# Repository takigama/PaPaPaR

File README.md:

# PaPaPaR

Short for Paste and Pick and Place and Reflow.

This project is an attempt to create a board that will do solder paste,
pick and place and lastly reflow. Initially I'll be aiming souly at the
pick and place stuff but theres enough componentry on the board to
control the paste and reflow components as well.

It does have enough componentry to also do a single extruder 3d printer
which wasnt exactly a goal, but was a handy alternative function for
the board. 

The board itself is reasonably compact but not a huge amount of work
has gone into it yet.

## Usage

Well, none yet. Haven't even printed the board yet. Currently using
RAMPS as a test bed.

This project is based on the STM32F103 chip and will (at least
initially) use the STM32duino code base with the arduino software
stack for making the thing "go"

You'll need kicad if you want to see the board and once i have a
working model, i'll share it as a project on oshpark!

## Thanks

Thanks go to the folk who do arduino, the folk who do stm32duino, to
the folk who do KiCad and many others probably. As of the current version
the only hardware designer is me... Im also the only coder... and the only
everything else but would welcome others

## Where it starts

The first version will be quite simple. Designed to be controlled with
2 "wiichucks", there is an expectation of having a camera and the pick
and place will be done "manually" but all electrically - i.e. you'll
place componets using joystick with some interesting hot keys and a bit
of camera work.

## It Looks Like This:

## What you need

- 3 Steppers (one for the pump)
- Perastaltic pump that can be driving by stepper (or 5-6v DC)
- a pick-up sucktion cup (i have a design for this thats really simple)
- a usb microscope.
- a design for it all to sit on
- a fair amount of imagination and pixie dust!
- a 12v power source

The pump (which is used to hold components) can either be stepper driven
or you can find plenty of 5-6v aquarium pumps on ebay that should surfice
but they want to be less than 1A.

Currently im working on the design of the actual platform for the whole
unit and it will look like a distant cousin of something like the mendel
90 (my fave 3d print) but with a stationary platform and a cartesian type
head. I was VERY tempted to do a delta but am shelving that idea for now

Currently there also exists no code but watch this space - some will
definitely be borrowed from the sprinter/marlin code bases but no code
yet exists.

## Things To Note

1. Its designed to be possible to hand solder (which is how I will build
it)

2. I take no responsibility if it does anything negative!

3. Its alpha

4. Im not the worlds greatest hardware designer (or even a good one)!

5. Currently doesnt have a license - feel free to do as you will, but will
ultimately be licensed under a compatible open source license (GPL for code
as an example)

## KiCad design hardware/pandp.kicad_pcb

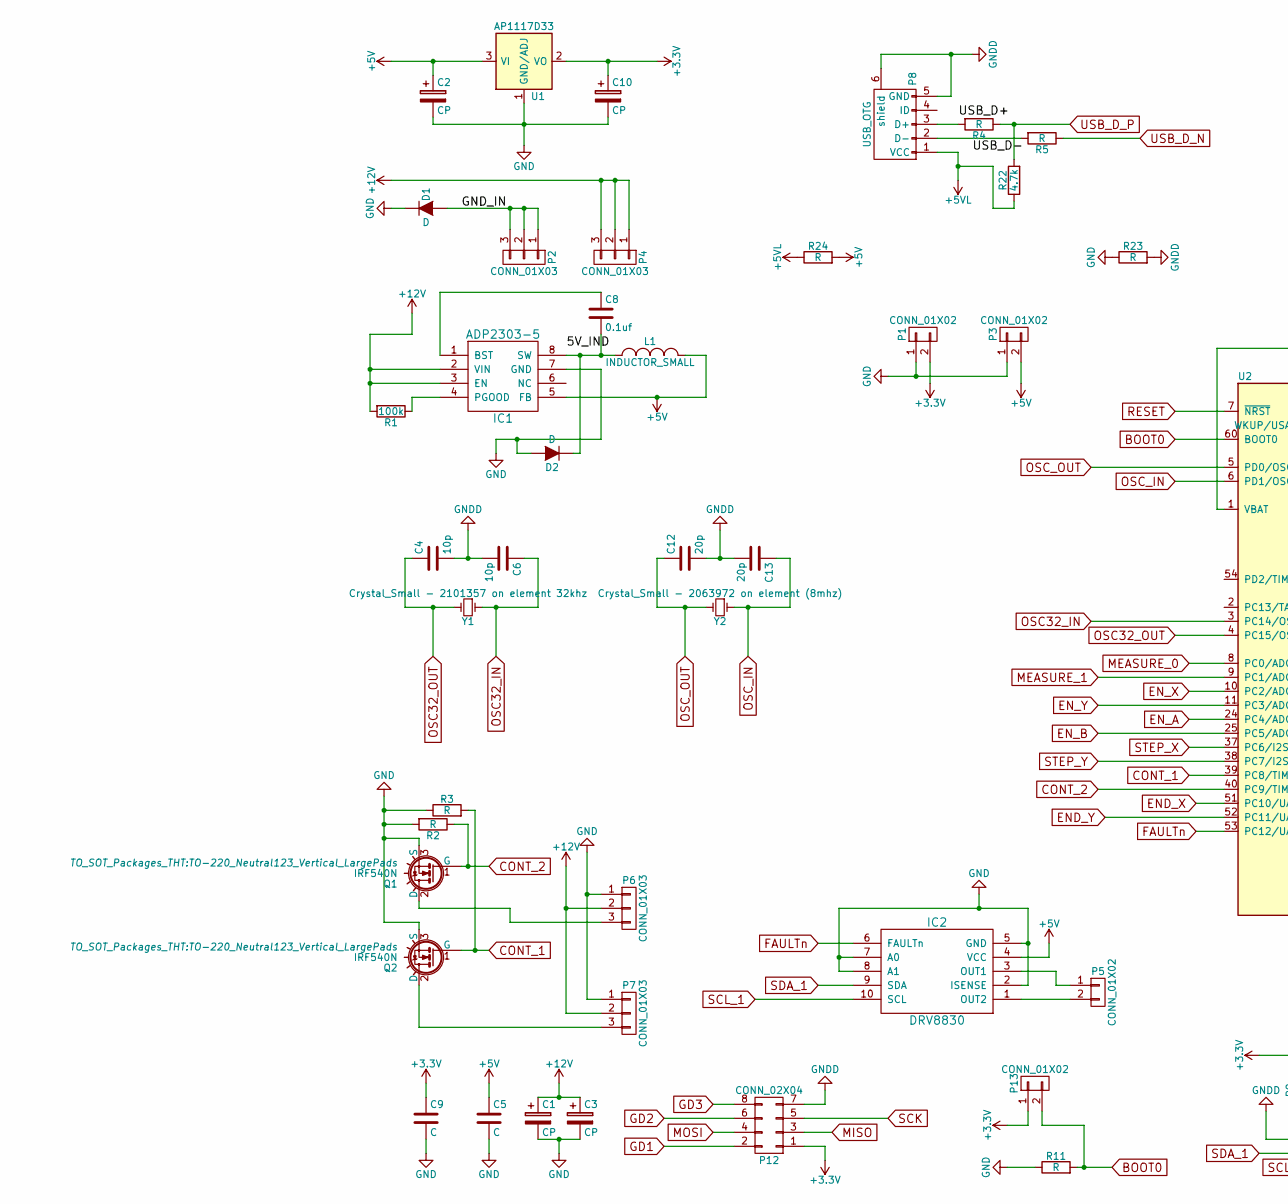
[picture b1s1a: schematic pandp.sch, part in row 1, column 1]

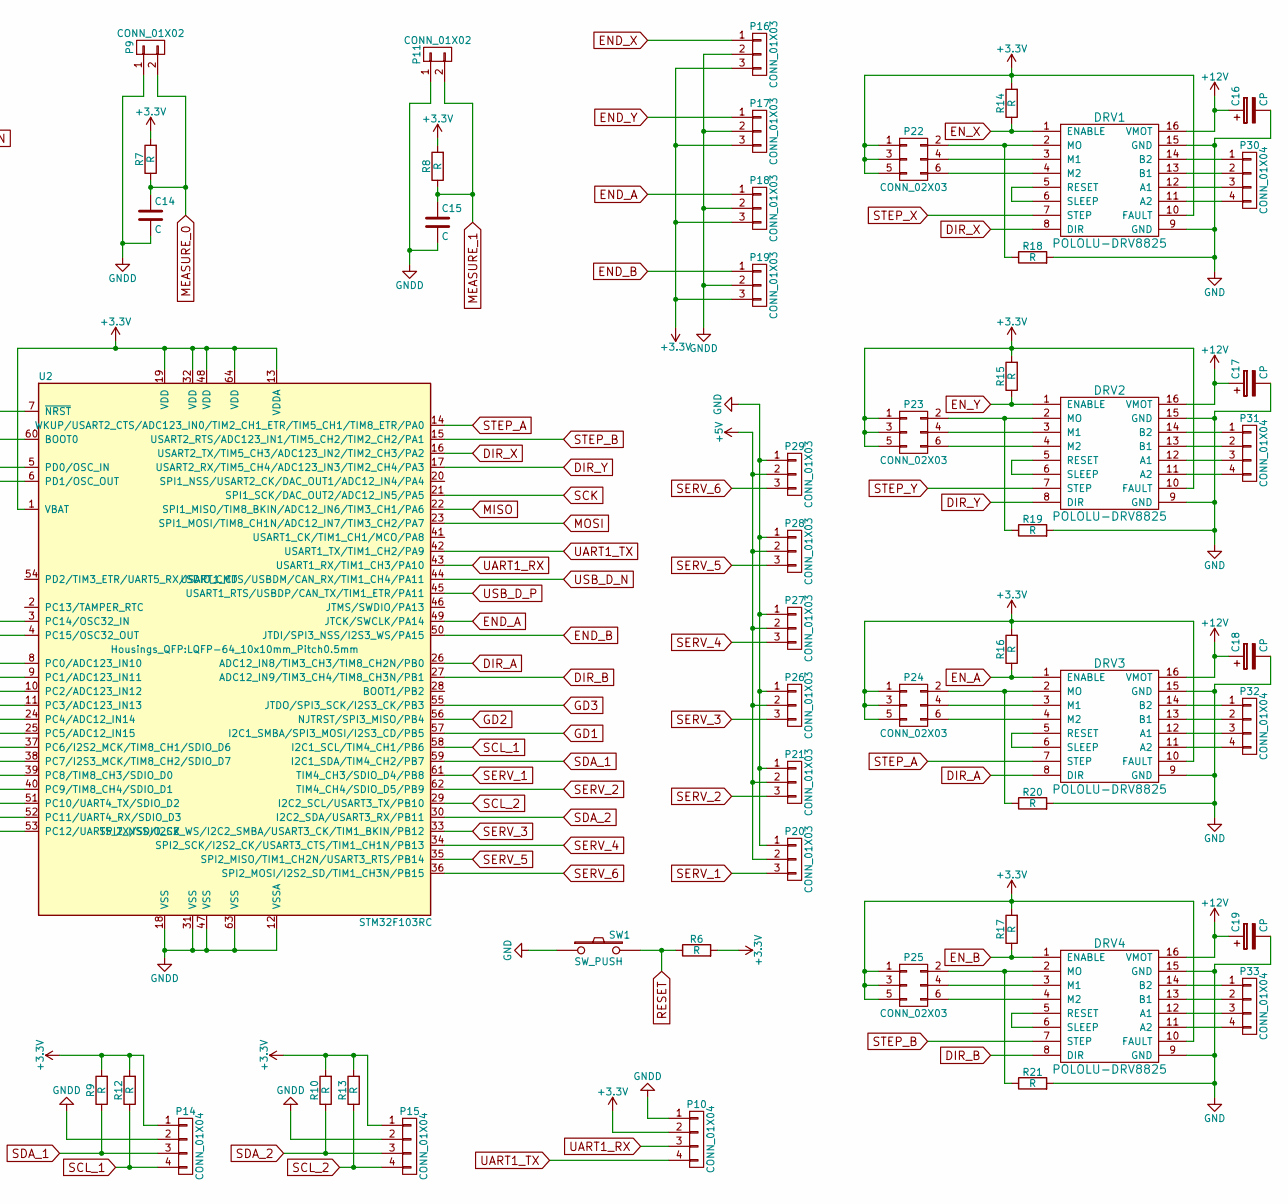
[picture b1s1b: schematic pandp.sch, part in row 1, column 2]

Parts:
C1, C2, C3, C10, C16, C17, C18, C19: CP; SMD-1210_Pol
C4, C6: 10p; C_0805_HandSoldering
C5, C9, C14, C15: C; C_0805_HandSoldering
C8: 0.1uf; C_0805_HandSoldering
C12, C13: 20p; C_0805_HandSoldering
D1, D2: D; SMB_Handsoldering
DRV1, DRV2, DRV3, DRV4: POLOLU-DRV8825
IC1: ADP2303-5; SOIC-8_3.9x4.9mm_Pitch1.27mm
IC2: DRV8830; TSSOP-10_3x3mm_Pitch0.5mm
L1: INDUCTOR_SMALL; Choke_SMD_7.3x7.3_H3.5
P1, P3, P5, P9, P11, P13: CONN_01X02; Pin_Header_Straight_1x02
P2, P4, P6, P7, P16, P17, P18, P19, P20, P21, P26, P27, P28, P29: CONN_01X03; Pin_Header_Straight_1x03
P8: USB_OTG; USB_Micro-B-OshPark
P10, P14, P15, P30, P31, P32, P33: CONN_01X04; Pin_Header_Straight_1x04
P12: CONN_02X04; Pin_Header_Straight_2x04
P22, P23, P24, P25: CONN_02X03; Pin_Header_Straight_2x03
Q1, Q2: IRF540N; TO-220_Neutral123_Vertical_LargePads
R1: 100k; R_0805_HandSoldering
R2, R3, R4, R5, R6, R7, R8, R9, R10, R11, R12, R13, R14, R15, R16, R17, R18, R19, R20, R21: R; R_0805_HandSoldering
R22: 4.7k; R_0805_HandSoldering
R23, R24: R; R_0402
SW1: SW_PUSH; SW_SPST_FSMSM
U1: AP1117D33; SOT-223
U2: STM32F103RC; LQFP-64_10x10mm_Pitch0.5mm
Y1: Crystal_Small - 2101357 on element 32khz; ABM3
Y2: Crystal_Small - 2063972 on element (8mhz); Crystal_HC49-SD_SMD

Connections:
+3V3: C9.1, C10.1, DRV1.10 (FAULT), DRV2.10 (FAULT), DRV3.10 (FAULT), DRV4.10 (FAULT), P1.2, P10.2, P12.1, P13.1, P14.1, P15.1, P16.3, P17.3, P18.3, P19.3, P22.1, P22.3, P22.5, P23.1, P23.3, P23.5, P24.1, P24.3, P24.5, P25.1, P25.3, P25.5, R6.2, R7.2, R8.2, R9.2, R10.2, R12.2, R13.2, R14.2, R15.2, R16.2, R17.2, U1.2 (VO), U2.1 (VBAT), U2.13 (VDDA), U2.19 (VDD), U2.32 (VDD), U2.48 (VDD), U2.64 (VDD)
+5V: C2.1, C5.1, IC1.5 (FB), IC2.4 (VCC), L1.2, P3.2, P20.2, P21.2, P26.2, P27.2, P28.2, P29.2, R24.2, U1.3 (VI)
+5VL: P8.1 (VCC), R22.1, R24.1
+12V: C1.1, C3.1, C16.1, C17.1, C18.1, C19.1, DRV1.16 (VMOT), DRV2.16 (VMOT), DRV3.16 (VMOT), DRV4.16 (VMOT), IC1.2 (VIN), IC1.3 (EN), P4.1, P4.2, P4.3, P6.2, P7.2, R1.2
/GND_IN: D1.2 (A), P2.1, P2.2, P2.3
BOOT0: P13.2, R11.2, U2.60 (BOOT0)
CONT_1: Q2.1 (G), R3.2, U2.39 (PC8/TIM8_CH3/SDIO_D0)
CONT_2: Q1.1 (G), R2.1, U2.40 (PC9/TIM8_CH4/SDIO_D1)
DIR_A: DRV3.8 (DIR), U2.26 (ADC12_IN8/TIM3_CH3/TIM8_CH2N/PB0)
DIR_B: DRV4.8 (DIR), U2.27 (ADC12_IN9/TIM3_CH4/TIM8_CH3N/PB1)
DIR_X: DRV1.8 (DIR), U2.16 (USART2_TX/TIM5_CH3/ADC123_IN2/TIM2_CH3/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)
DIR_Y: DRV2.8 (DIR), U2.17 (USART2_RX/TIM5_CH4/ADC123_IN3/TIM2_CH4/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)
END_A: P18.1, U2.49 (JTCK/SWCLK/PA14)
END_B: P19.1, U2.50 (JTDI/SPI3_NSS/I2S3_WS/PA15)
END_X: P16.1, U2.51 (PC10/UART4_TX/SDIO_D2)
END_Y: P17.1, U2.52 (PC11/UART4_RX/SDIO_D3)
EN_A: DRV3.1 (ENABLE), R16.1, U2.24 (PC4/ADC12_IN14)
EN_B: DRV4.1 (ENABLE), R17.1, U2.25 (PC5/ADC12_IN15)
EN_X: DRV1.1 (ENABLE), R14.1, U2.10 (PC2/ADC123_IN12)
EN_Y: DRV2.1 (ENABLE), R15.1, U2.11 (PC3/ADC123_IN13)
FAULTn: IC2.6 (FAULTn), U2.53 (PC12/UART5_TX/SDIO_CK)
GD1: P12.2, U2.57 (I2C1_SMBA/SPI3_MOSI/I2S3_CD/PB5)
GD2: P12.6, U2.56 (NJTRST/SPI3_MISO/PB4)
GD3: P12.8, U2.55 (JTDO/SPI3_SCK/I2S3_CK/PB3)
GND: C1.2, C2.2, C3.2, C5.2, C9.2, C10.2, C16.2, C17.2, C18.2, C19.2, D1.1 (K), D2.2 (A), DRV1.9 (GND), DRV1.15 (GND), DRV2.9 (GND), DRV2.15 (GND), DRV3.9 (GND), DRV3.15 (GND), DRV4.9 (GND), DRV4.15 (GND), IC1.7 (GND), IC2.2 (ISENSE), IC2.5 (GND), IC2.7 (A0), IC2.8 (A1), P1.1, P3.1, P6.1, P7.1, P20.1, P21.1, P26.1, P27.1, P28.1, P29.1, Q1.3 (S), Q2.3 (S), R2.2, R3.1, R11.1, R18.2, R19.2, R20.2, R21.2, R23.1, SW1.1, U1.1 (GND/ADJ)
GNDD: C4.2, C6.2, C12.2, C13.2, C14.2, C15.2, P8.5 (GND), P8.6 (shield), P9.1, P10.1, P11.1, P12.7, P14.2, P15.2, P16.2, P17.2, P18.2, P19.2, R23.2, U2.12 (VSSA), U2.18 (VSS), U2.31 (VSS), U2.47 (VSS), U2.63 (VSS)
MEASURE_0: C14.1, P9.2, R7.1, U2.8 (PC0/ADC123_IN10)
MEASURE_1: C15.1, P11.2, R8.1, U2.9 (PC1/ADC123_IN11)
MISO: P12.3, U2.22 (SPI1_MISO/TIM8_BKIN/ADC12_IN6/TIM3_CH1/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)
MOSI: P12.4, U2.23 (SPI1_MOSI/TIM8_CH1N/ADC12_IN7/TIM3_CH2/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)
unnamed: C8.1, IC1.1 (BST)
unnamed: C8.2, D2.1 (K), IC1.8 (SW), L1.1
unnamed: DRV1.2 (MO), P22.2, R18.1
unnamed: DRV1.3 (M1), P22.4
unnamed: DRV1.4 (M2), P22.6
unnamed: DRV1.5 (RESET), DRV1.6 (SLEEP)
unnamed: DRV1.11 (A2), P30.4
unnamed: DRV1.12 (A1), P30.3
unnamed: DRV1.13 (B1), P30.2
unnamed: DRV1.14 (B2), P30.1
unnamed: DRV2.2 (MO), P23.2, R19.1
unnamed: DRV2.3 (M1), P23.4
unnamed: DRV2.4 (M2), P23.6
unnamed: DRV2.5 (RESET), DRV2.6 (SLEEP)
unnamed: DRV2.11 (A2), P31.4
unnamed: DRV2.12 (A1), P31.3
unnamed: DRV2.13 (B1), P31.2
unnamed: DRV2.14 (B2), P31.1
unnamed: DRV3.2 (MO), P24.2, R20.1
unnamed: DRV3.3 (M1), P24.4
unnamed: DRV3.4 (M2), P24.6
unnamed: DRV3.5 (RESET), DRV3.6 (SLEEP)
unnamed: DRV3.11 (A2), P32.4
unnamed: DRV3.12 (A1), P32.3
unnamed: DRV3.13 (B1), P32.2
unnamed: DRV3.14 (B2), P32.1
unnamed: DRV4.2 (MO), P25.2, R21.1
unnamed: DRV4.3 (M1), P25.4
unnamed: DRV4.4 (M2), P25.6
unnamed: DRV4.5 (RESET), DRV4.6 (SLEEP)
unnamed: DRV4.11 (A2), P33.4
unnamed: DRV4.12 (A1), P33.3
unnamed: DRV4.13 (B1), P33.2
unnamed: DRV4.14 (B2), P33.1
unnamed: IC1.4 (PGOOD), R1.1
unnamed: IC2.1 (OUT2), P5.2
unnamed: IC2.3 (OUT1), P5.1
unnamed: P6.3, Q1.2 (D)
unnamed: P7.3, Q2.2 (D)
unnamed: P8.2 (D-), R5.2
unnamed: P8.3 (D+), R4.2
OSC32_IN: C6.1, U2.3 (PC14/OSC32_IN), Y1.1
OSC32_OUT: C4.1, U2.4 (PC15/OSC32_OUT), Y1.2
OSC_IN: C13.1, U2.6 (PD1/OSC_OUT), Y2.1
OSC_OUT: C12.1, U2.5 (PD0/OSC_IN), Y2.2
RESET: R6.1, SW1.2, U2.7 (~NRST)
SCK: P12.5, U2.21 (SPI1_SCK/DAC_OUT2/ADC12_IN5/PA5)
SCL_1: IC2.10 (SCL), P14.4, R12.1, U2.58 (I2C1_SCL/TIM4_CH1/PB6)
SCL_2: P15.4, R13.1, U2.29 (I2C2_SCL/USART3_TX/PB10)
SDA_1: IC2.9 (SDA), P14.3, R9.1, U2.59 (I2C1_SDA/TIM4_CH2/PB7)
SDA_2: P15.3, R10.1, U2.30 (I2C2_SDA/USART3_RX/PB11)
SERV_1: P20.3, U2.61 (TIM4_CH3/SDIO_D4/PB8)
SERV_2: P21.3, U2.62 (TIM4_CH4/SDIO_D5/PB9)
SERV_3: P26.3, U2.33 (SPI2_NSS/I2S2_WS/I2C2_SMBA/USART3_CK/TI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)
SERV_4: P27.3, U2.34 (SPI2_SCK/I2S2_CK/USART3_CTS/TIM1_CH1N/P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)
SERV_5: P28.3, U2.35 (SPI2_MISO/TIM1_CH2N/USART3_RTS/PB14)
SERV_6: P29.3, U2.36 (SPI2_MOSI/I2S2_SD/TIM1_CH3N/PB15)
STEP_A: DRV3.7 (STEP), U2.14 (WKUP/USART2_CTS/ADC123_IN0/TIM2_CH1_ETR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)
STEP_B: DRV4.7 (STEP), U2.15 (USART2_RTS/ADC123_IN1/TIM5_CH2/TIM2_CH2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)
STEP_X: DRV1.7 (STEP), U2.37 (PC6/I2S2_MCK/TIM8_CH1/SDIO_D6)
STEP_Y: DRV2.7 (STEP), U2.38 (PC7/I2S3_MCK/TIM8_CH2/SDIO_D7)
UART1_RX: P10.3, U2.43 (USART1_RX/TIM1_CH3/PA10)
UART1_TX: P10.4, U2.42 (USART1_TX/TIM1_CH2/PA9)
USB_D_N: R5.1, U2.44 (USART1_CTS/USBDM/CAN_RX/TIM1_CH4/PA11)
USB_D_P: R4.1, R22.2, U2.45 (USART1_RTS/USBDP/CAN_TX/TIM1_ETR/PA11)

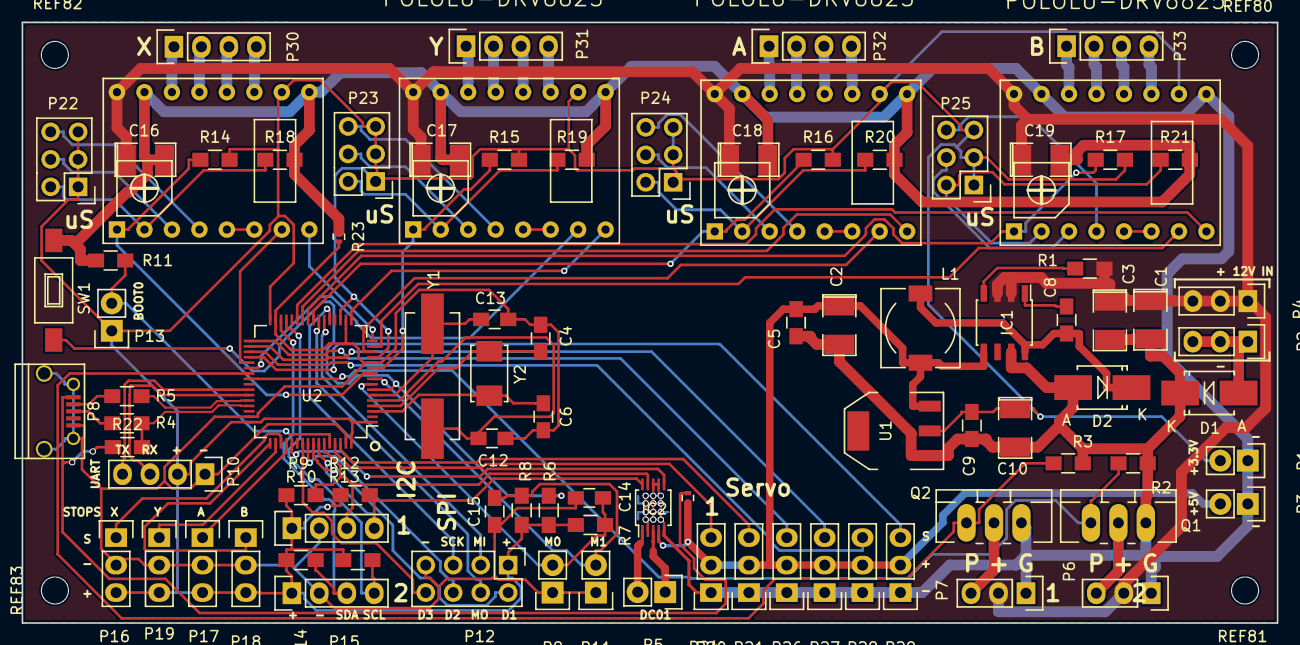
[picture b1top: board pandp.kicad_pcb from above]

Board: 2 copper layers, 116.0 x 55.5 mm, 94 parts (0 on the bottom side), 95 nets.

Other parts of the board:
REF80, REF81, REF82, REF83: MountingHole_2-5mm

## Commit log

2016-10-05 Initial PaPPaR import
2016-10-06 first autorouter - dont like
2016-10-06 power self-routed
2016-10-07 pre-route-import
2016-10-07 final - V1
2016-10-07 Moving to new layout
2016-10-07 added a readme - prepping for github
2016-10-07 rename dir
2016-10-07 minor change to board text
2016-10-11 added 5v dc motor control - low current - 500ma or less
2016-10-11 images and readme update
2016-10-11 Readme update
2016-10-12 oshpark compatible holes for uusb connector
2016-10-12 new uusb oshpark compatible, added a mark for the stm chip pin 0
2016-10-15 added pullup for usb
2016-10-16 removed the terrible frame from hell
2016-10-16 changed a few small routes, added vias for cooling on dc conroller
